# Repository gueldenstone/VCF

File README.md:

# VCF
Voltage Controlled State Variable Filter for Eurorack

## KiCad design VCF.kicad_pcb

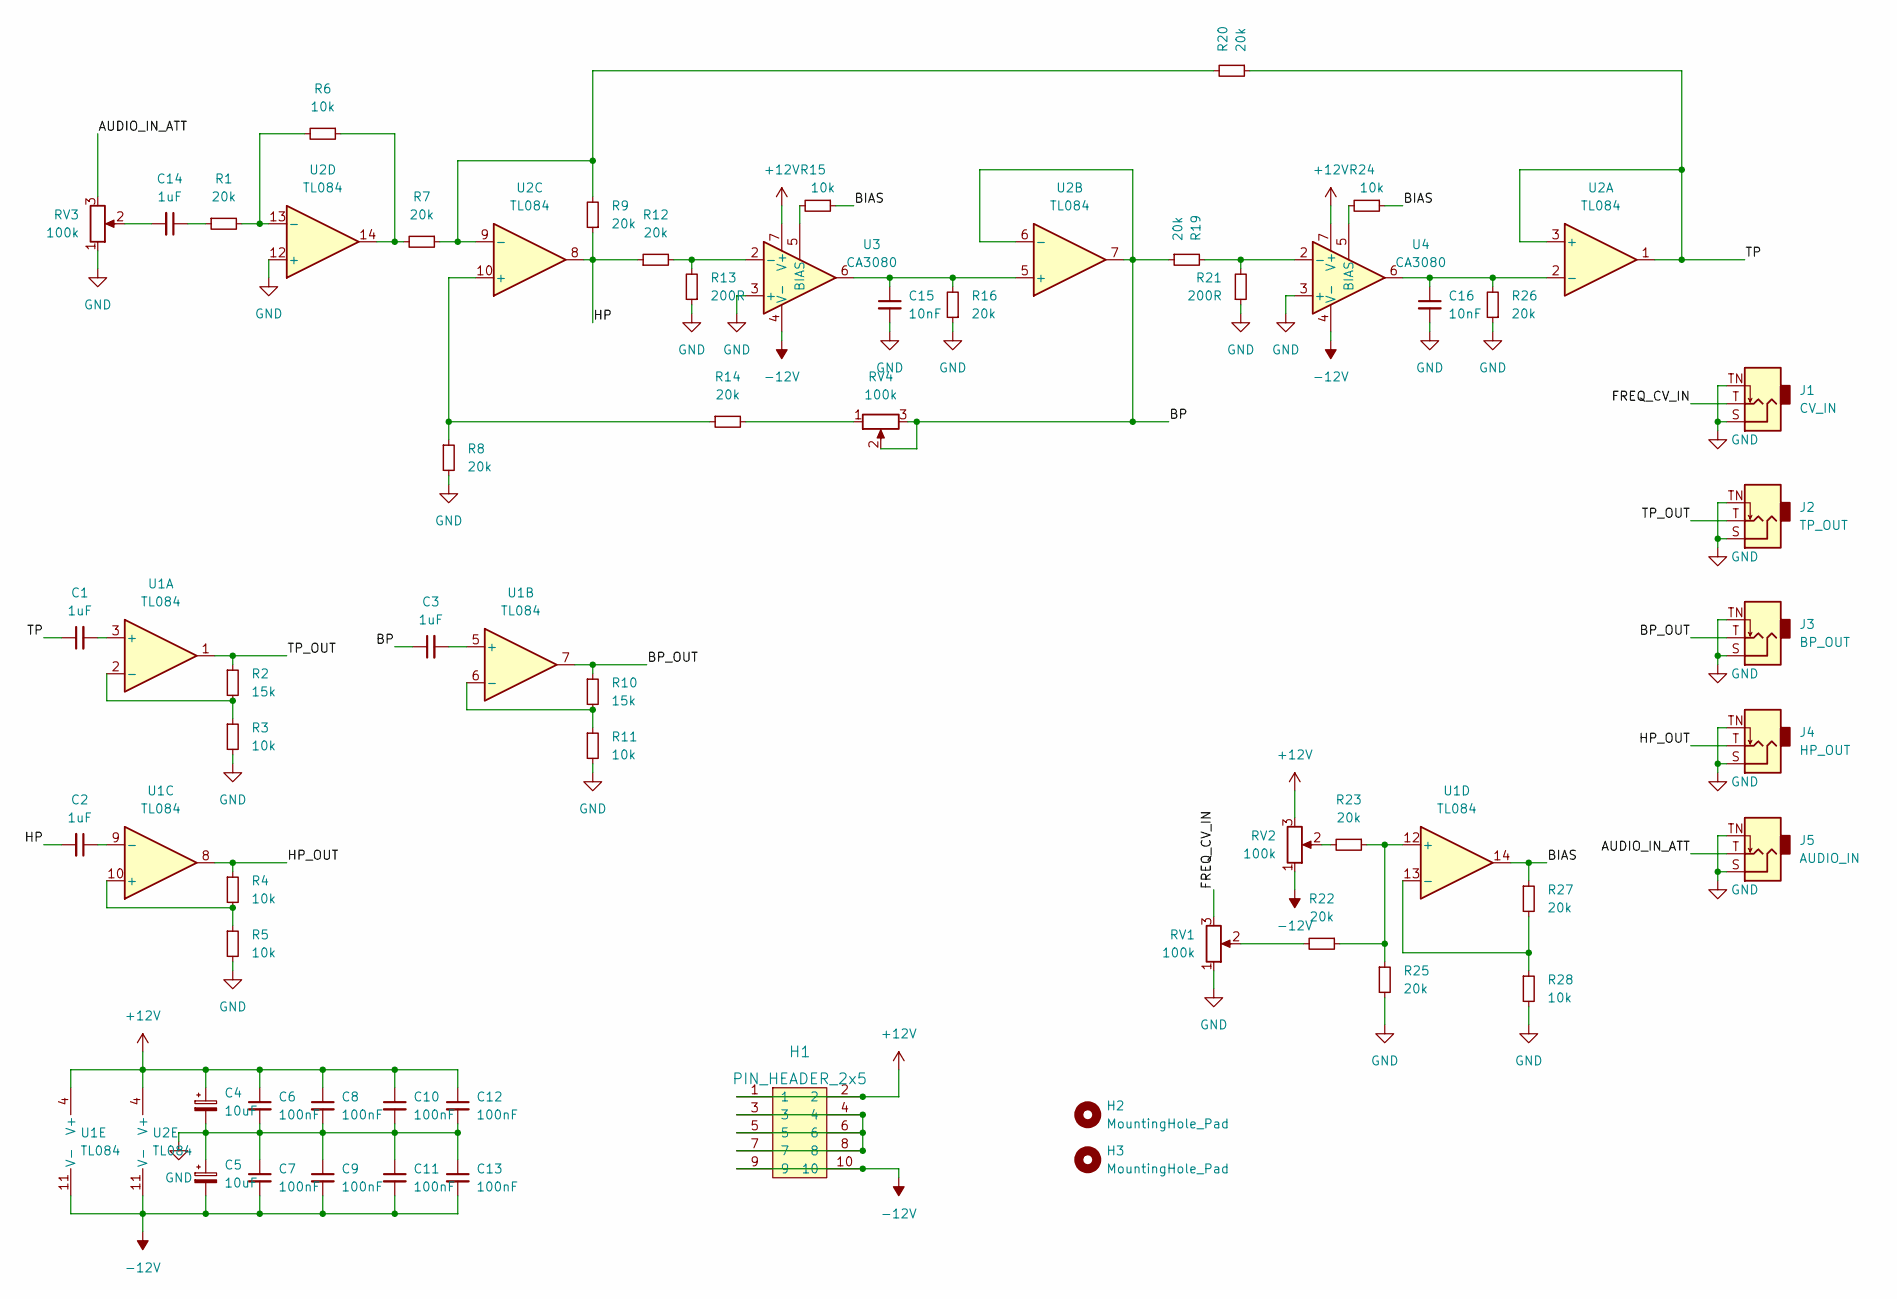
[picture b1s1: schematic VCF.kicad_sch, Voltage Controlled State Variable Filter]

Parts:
C1, C2, C3, C14: 1uF; C_Rect_L7.2mm_W4.5mm_P5.00mm_FKS2_FKP2_MKS2_MKP2
C4, C5: 10uF; CP_Radial_D6.3mm_P2.50mm
C6, C7, C8, C9, C10, C11, C12, C13: 100nF; C_Rect_L7.2mm_W3.0mm_P5.00mm_FKS2_FKP2_MKS2_MKP2
C15, C16: 10nF; C_Rect_L7.2mm_W3.0mm_P5.00mm_FKS2_FKP2_MKS2_MKP2
H1: PIN_HEADER_2x5; PinHeader_2x05_P2.54mm_Vertical
H2, H3: MountingHole_Pad; MountingHole_3.2mm_M3_DIN965
J1: CV_IN; Jack_3.5mm_QingPu_WQP-PJ398SM_Vertical_CircularHoles
J2: TP_OUT; Jack_3.5mm_QingPu_WQP-PJ398SM_Vertical_CircularHoles
J3: BP_OUT; Jack_3.5mm_QingPu_WQP-PJ398SM_Vertical_CircularHoles
J4: HP_OUT; Jack_3.5mm_QingPu_WQP-PJ398SM_Vertical_CircularHoles
J5: AUDIO_IN; Jack_3.5mm_QingPu_WQP-PJ398SM_Vertical_CircularHoles
R1, R7, R8, R9, R12, R14, R16, R19, R20, R22, R23, R25, R26, R27: 20k; R_Axial_DIN0207_L6.3mm_D2.5mm_P10.16mm_Horizontal
R2, R10: 15k; R_Axial_DIN0207_L6.3mm_D2.5mm_P10.16mm_Horizontal
R3, R4, R5, R6, R11, R15, R24, R28: 10k; R_Axial_DIN0207_L6.3mm_D2.5mm_P10.16mm_Horizontal
R13, R21: 200R; R_Axial_DIN0207_L6.3mm_D2.5mm_P10.16mm_Horizontal
RV1, RV2, RV3, RV4: 100k; Potentiometer_Alpha_RD901F-40-00D_Single_Vertical_CircularH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
U1, U2: TL084; DIP-14_W7.62mm_Socket
U3, U4: CA3080; DIP-8_W7.62mm_Socket

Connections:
+12V: C4.1, C6.1, C8.1, C10.1, C12.1, H1.1, H1.2, RV2.3, U1.4 (V+), U2.4 (V+), U3.7 (V+), U4.7 (V+)
-12V: C5.2, C7.2, C9.2, C11.2, C13.2, H1.9, H1.10, RV2.1, U1.11 (V-), U2.11 (V-), U3.4 (V-), U4.4 (V-)
/AUDIO_IN_ATT: J5.T, RV3.3
/BIAS: R15.1, R24.1, R27.1, U1.14
/BP: C3.1, R19.1, RV4.2, RV4.3, U2.6 (-), U2.7
/BP_OUT: J3.T, R10.1, U1.7
/FREQ_CV_IN: J1.T, RV1.3
/HP: C2.2, R9.1, R12.1, U2.8
/HP_OUT: J4.T, R4.1, U1.8
/TP: C1.1, R20.1, U2.1, U2.3 (+)
/TP_OUT: J2.T, R2.1, U1.1
GND: C4.2, C5.1, C6.2, C7.1, C8.2, C9.1, C10.2, C11.1, C12.2, C13.1, C15.2, C16.2, J1.S, J1.TN, J2.S, J2.TN, J3.S, J3.TN, J4.S, J4.TN, J5.S, J5.TN, R3.2, R5.2, R8.2, R11.2, R13.1, R16.1, R21.1, R25.2, R26.1, R28.2, RV1.1, RV3.1, U2.12 (+), U3.3 (+), U4.3 (+)
unnamed: C1.2, U1.3 (+)
unnamed: C2.1, U1.9 (-)
unnamed: C3.2, U1.5 (+)
unnamed: C14.1, R1.1
unnamed: C14.2, RV3.2
unnamed: C15.1, R16.2, U2.5 (+), U3.6
unnamed: C16.1, R26.2, U2.2 (-), U4.6
unnamed: H1.3, H1.4, H1.5, H1.6, H1.7, H1.8
unnamed: R1.2, R6.2, U2.13 (-)
unnamed: R2.2, R3.1, U1.2 (-)
unnamed: R4.2, R5.1, U1.10 (+)
unnamed: R6.1, R7.2, U2.14
unnamed: R10.2, R11.1, U1.6 (-)
unnamed: R12.2, R13.2, U3.2 (-)
unnamed: R8.1, R14.1, U2.10 (+)
unnamed: R14.2, RV4.1
unnamed: R15.2, U3.5 (BIAS)
unnamed: R19.2, R21.2, U4.2 (-)
unnamed: R7.1, R9.2, R20.2, U2.9 (-)
unnamed: R22.1, R23.1, R25.1, U1.12 (+)
unnamed: R22.2, RV1.2
unnamed: R23.2, RV2.2
unnamed: R24.2, U4.5 (BIAS)
unnamed: R27.2, R28.1, U1.13 (-)

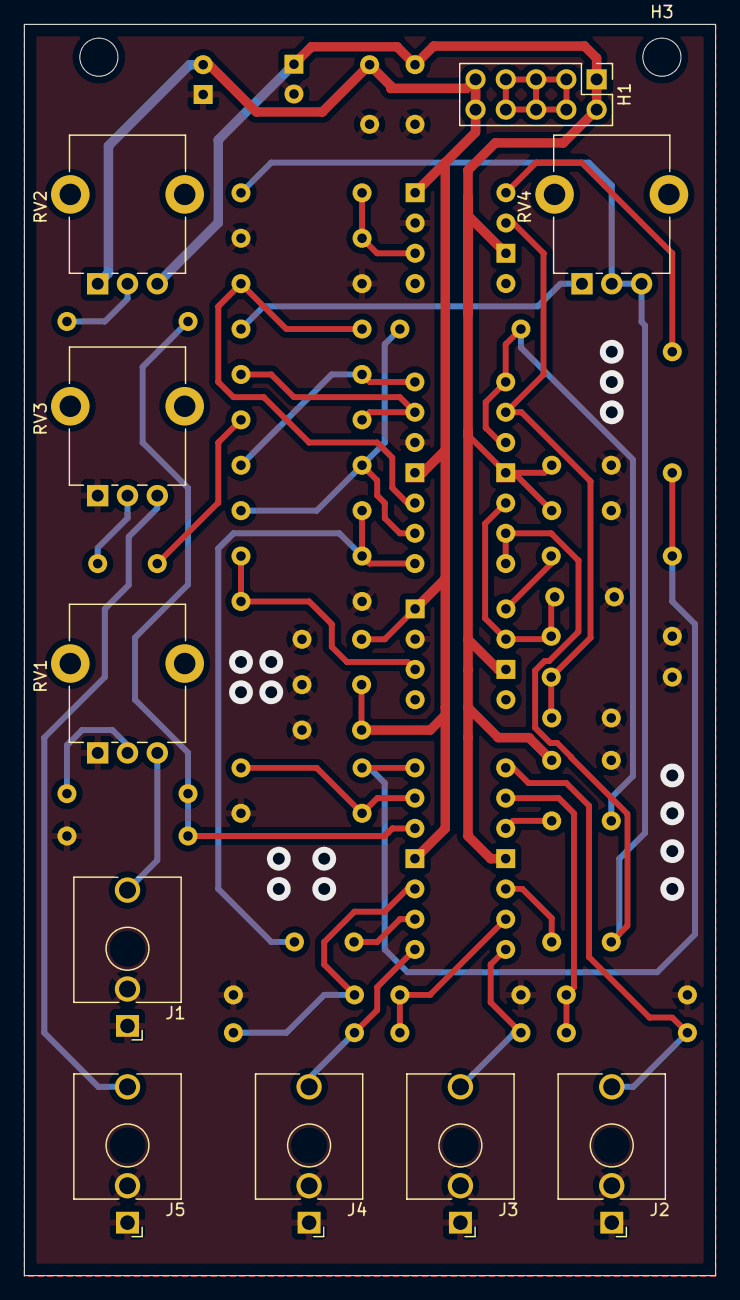
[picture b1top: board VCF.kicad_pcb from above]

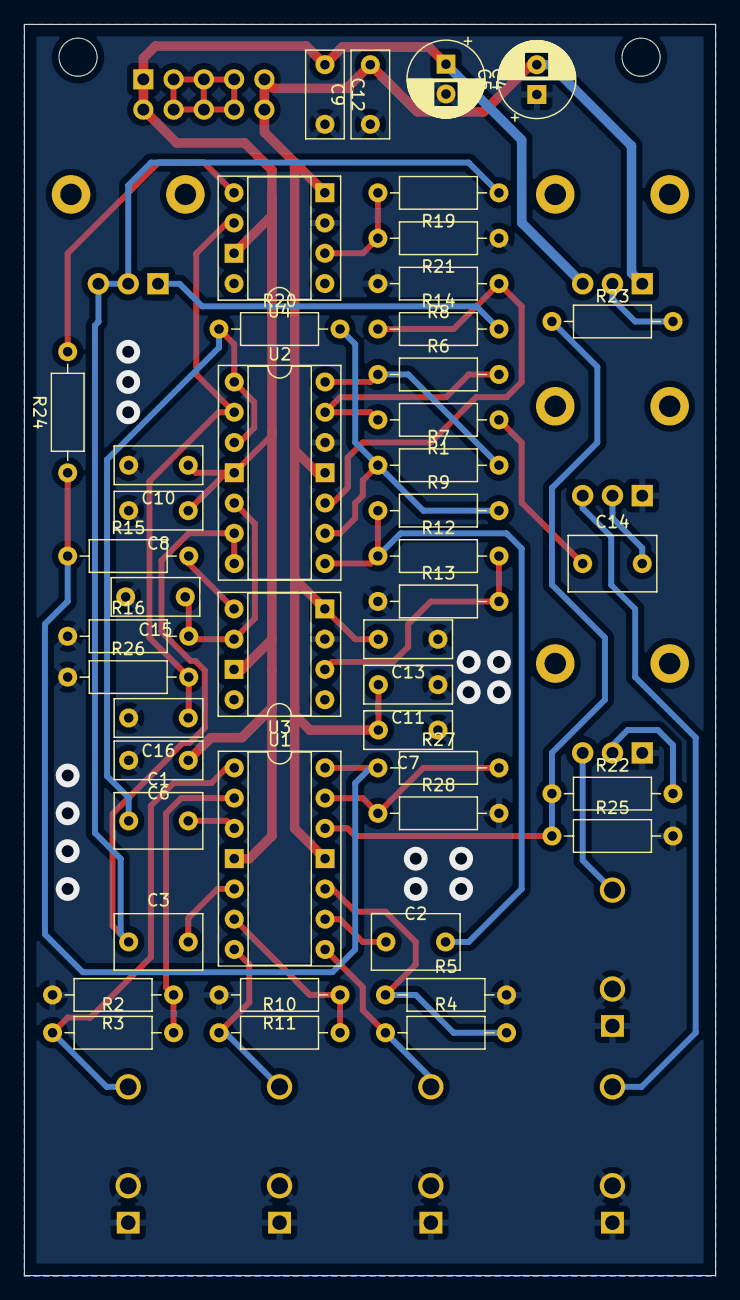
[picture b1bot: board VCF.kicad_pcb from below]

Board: 2 copper layers, 58.0 x 105.0 mm, 58 parts (46 on the bottom side), 36 nets.

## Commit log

2022-05-14 Adds eurocad lib as submodule
2022-05-14 Prototype 1
2022-05-16 Replace schematic
2022-05-16 finish schematic and begin pcb
2022-05-17 Add files via upload
    First Layout Draft (Not Complete!)
    Current File: VCF. Only for measuring the layout
2022-05-17 Poti Positioning
2022-05-17 Adds frontpanel
2022-05-17 Prototype #1
    Layout and Schematics Done.
    Please ignore Silkscreen, SolderPaste and Courtyard warnings; won't be manufactured!
    Check M3 mounting hole size and position and the GND Vias!
2022-05-18 Update frontpanel with positions from finished pcb
2022-05-18 Add files via upload
    Updated Capacitors to be all on on the bottom layer and all it's conducting paths on the top layer. This uses two VIAs extra VIAs for the signal paths.
2022-05-19 Final version 1
2022-06-16 Final v2
